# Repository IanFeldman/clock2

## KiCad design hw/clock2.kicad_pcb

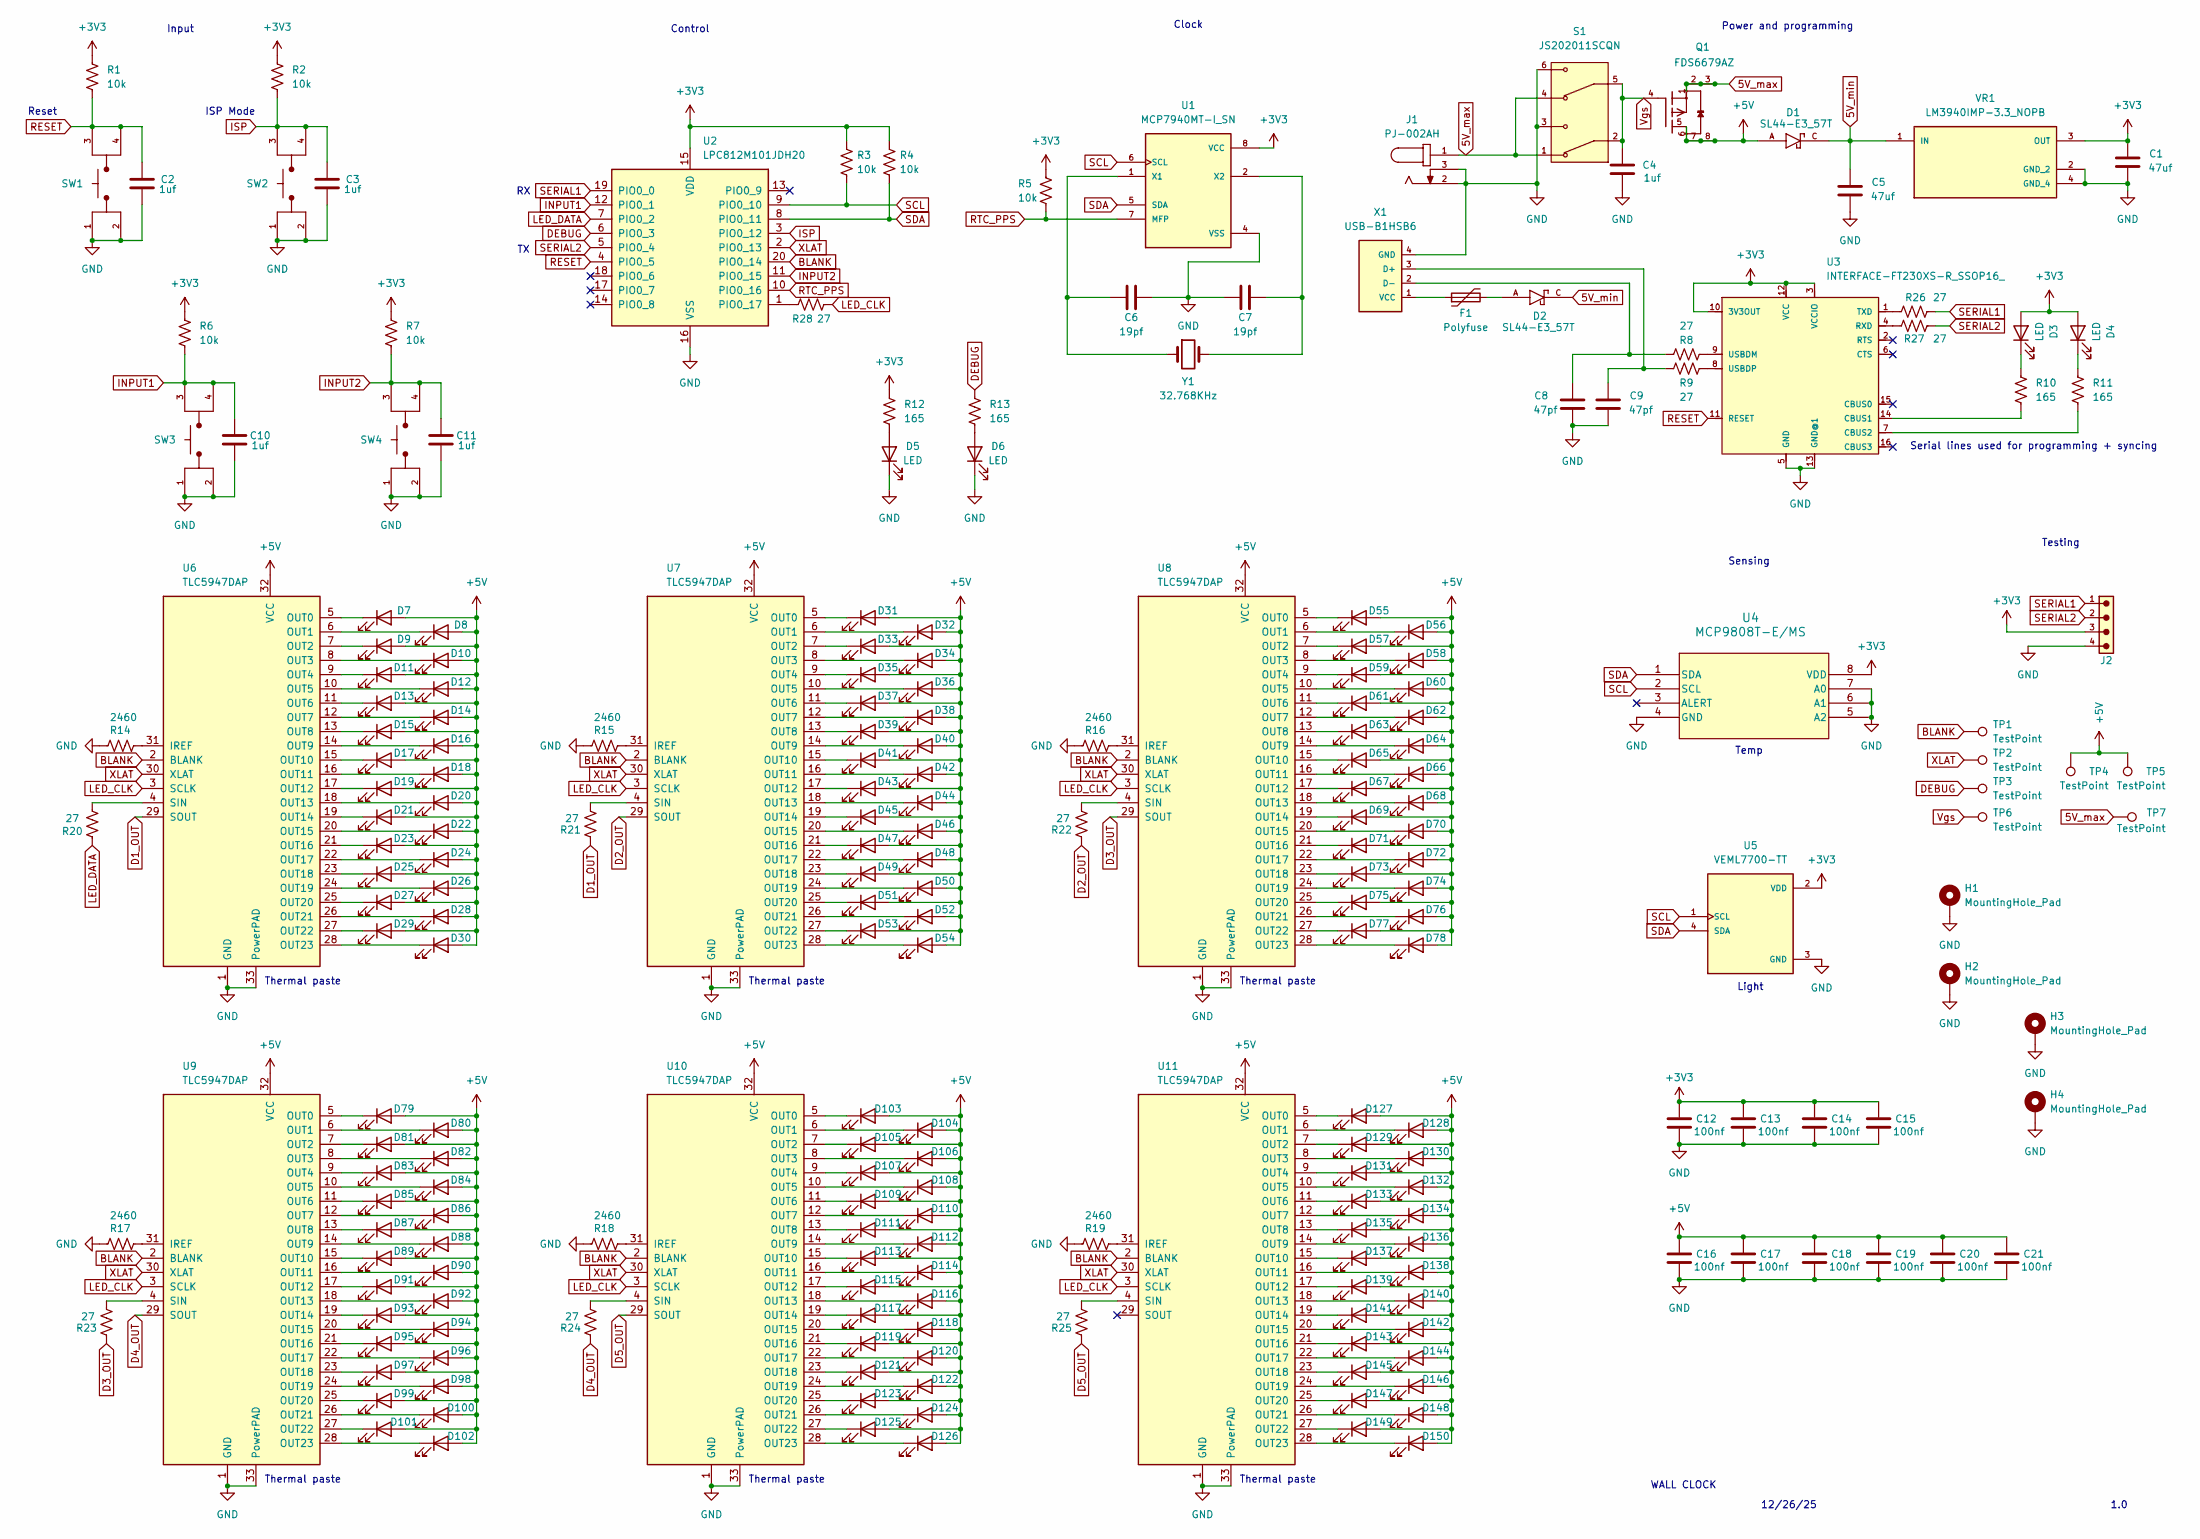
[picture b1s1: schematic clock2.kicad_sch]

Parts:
C1, C5: 47uf; C_0805_2012Metric
C2, C3, C4, C10, C11: 1uf; C_0805_2012Metric
C6, C7: 19pf; C_0805_2012Metric
C8, C9: 47pf; C_0805_2012Metric
C12, C13, C14, C15, C16, C17, C18, C19, C20, C21: 100nf; C_0805_2012Metric
D1, D2: SL44-E3_57T; DIOM7959X262N; DigiKey_Part_Number SL44-E3/57TGICT-ND
D3, D4, D5, D6: LED; LED_0805_2012Metric
D7, D8, D9, D10, D11, D12, D13, D14, D15, D16, D17, D18, D19, D20, D21, D22, D23, D24, D25, D26, D27, D28, D29, D30, D31, D32, D33, D34, D35, D36, D37, D38, D39, D40, D41, D42, D43, D44, D45, D46, D47, D48, D49, D50, D51, D52, D53, D54, D55, D56, D57, D58, D59, D60, D61, D62, D63, D64, D65, D66, D67, D68, D69, D70, D71, D72, D73, D74, D75, D76, D77, D78, D79, D80, D81, D82, D83, D84, D85, D86, D87, D88, D89, D90, D91, D92, D93, D94, D95, D96, D97, D98, D99, D100, D101, D102, D103, D104, D105, D106, D107, D108, D109, D110, D111, D112, D113, D114, D115, D116, D117, D118, D119, D120, D121, D122, D123, D124, D125, D126, D127, D128, D129, D130, D131, D132, D133, D134, D135, D136, D137, D138, D139, D140, D141, D142, D143, D144, D145, D146, D147, D148, D149, D150: LED; LED_1206_3216Metric
F1: Polyfuse; Fuse_1206_3216Metric
H1, H2, H3, H4: MountingHole_Pad; MountingHole_3.2mm_M3_DIN965_Pad
J1: PJ-002AH; CUI_PJ-002AH; DigiKey_Part_Number CP-002AH-ND
J2: 6130XX11121_61300411121; 61300411121
Q1: FDS6679AZ; SOIC127P600X175-8N; DigiKey_Part_Number FDS6679AZCT-ND
R1, R2, R3, R4, R5, R6, R7: 10k; R_0805_2012Metric
R8, R9, R20, R21, R22, R23, R24, R25, R26, R27, R28: 27; R_0805_2012Metric
R10, R11, R12, R13: 165; R_0805_2012Metric
R14, R15, R16, R17, R18, R19: 2460; R_0805_2012Metric
S1: JS202011SCQN; SW_JS202011SCQN; PARTREV 1.01
SW1, SW2, SW3, SW4: TL3305AF260QG; SW_TL3305AF260QG; PARTREV C
TP1, TP2, TP3, TP4, TP5, TP6, TP7: TestPoint; HARWIN_S1751-46R
U1: MCP7940MT-I_SN; SOIC127P600X175-8N
U2: LPC812M101JDH20; TSSOP-20_4.4x6.5mm_P0.65mm
U3: INTERFACE-FT230XS-R_SSOP16_; SSOP16-0.635-5X4MM; MPN FT230XS-R
U4: MCP9808T-E/MS; MCP9808T
U5: VEML7700-TT; XDCR_VEML7700-TT; PARTREV 1.6; DigiKey_Part_Number 751-VEML7700-TTCT-ND
U6, U7, U8, U9, U10, U11: TLC5947DAP; HTSSOP-32-1EP_6.1x11mm_P0.65mm_EP5.2x11mm_Mask4.11x4.36mm_T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
VR1: LM3940IMP-3.3_NOPB; VREG_LM3940IMP-3.3_NOPB; PARTREV G
X1: USB-B1HSB6; OST_USB-B1HSB6; DigiKey_Part_Number ED2983-ND
Y1: 32.768KHz; XTAL_ECS-.327-12.5-34RR-TR

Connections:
5V_max: J1.1, Q1.1, Q1.2, Q1.3, S1.1, S1.4, TP7.1
5V_min: C5.2, D1.C, D2.C, VR1.1 (IN)
+3V3: C1.2, C12.2, C13.2, C14.2, C15.2, D3.2 (A), D4.2 (A), J2.3, R1.2, R2.2, R3.2, R4.2, R5.2, R6.2, R7.2, R12.2, U1.8 (VCC), U2.15 (VDD), U3.3 (VCCIO), U3.10 (3V3OUT), U3.12 (VCC), U4.8 (VDD), U5.2 (VDD), VR1.3 (OUT)
+5V: C16.2, C17.2, C18.2, C19.2, C20.2, C21.2, D1.A, D7.2 (A), D8.2 (A), D9.2 (A), D10.2 (A), D11.2 (A), D12.2 (A), D13.2 (A), D14.2 (A), D15.2 (A), D16.2 (A), D17.2 (A), D18.2 (A), D19.2 (A), D20.2 (A), D21.2 (A), D22.2 (A), D23.2 (A), D24.2 (A), D25.2 (A), D26.2 (A), D27.2 (A), D28.2 (A), D29.2 (A), D30.2 (A), D31.2 (A), D32.2 (A), D33.2 (A), D34.2 (A), D35.2 (A), D36.2 (A), D37.2 (A), D38.2 (A), D39.2 (A), D40.2 (A), D41.2 (A), D42.2 (A), D43.2 (A), D44.2 (A), D45.2 (A), D46.2 (A), D47.2 (A), D48.2 (A), D49.2 (A), D50.2 (A), D51.2 (A), D52.2 (A), D53.2 (A), D54.2 (A), D55.2 (A), D56.2 (A), D57.2 (A), D58.2 (A), D59.2 (A), D60.2 (A), D61.2 (A), D62.2 (A), D63.2 (A), D64.2 (A), D65.2 (A), D66.2 (A), D67.2 (A), D68.2 (A), D69.2 (A), D70.2 (A), D71.2 (A), D72.2 (A), D73.2 (A), D74.2 (A), D75.2 (A), D76.2 (A), D77.2 (A), D78.2 (A), D79.2 (A), D80.2 (A), D81.2 (A), D82.2 (A), D83.2 (A), D84.2 (A), D85.2 (A), D86.2 (A), D87.2 (A), D88.2 (A), D89.2 (A), D90.2 (A), D91.2 (A), D92.2 (A), D93.2 (A), D94.2 (A), D95.2 (A), D96.2 (A), D97.2 (A), D98.2 (A), D99.2 (A), D100.2 (A), D101.2 (A), D102.2 (A), D103.2 (A), D104.2 (A), D105.2 (A), D106.2 (A), D107.2 (A), D108.2 (A), D109.2 (A), D110.2 (A), D111.2 (A), D112.2 (A), D113.2 (A), D114.2 (A), D115.2 (A), D116.2 (A), D117.2 (A), D118.2 (A), D119.2 (A), D120.2 (A), D121.2 (A), D122.2 (A), D123.2 (A), D124.2 (A), D125.2 (A), D126.2 (A), D127.2 (A), D128.2 (A), D129.2 (A), D130.2 (A), D131.2 (A), D132.2 (A), D133.2 (A), D134.2 (A), D135.2 (A), D136.2 (A), D137.2 (A), D138.2 (A), D139.2 (A), D140.2 (A), D141.2 (A), D142.2 (A), D143.2 (A), D144.2 (A), D145.2 (A), D146.2 (A), D147.2 (A), D148.2 (A), D149.2 (A), D150.2 (A), Q1.5, Q1.6, Q1.7, Q1.8, TP4.1, TP5.1, U6.32 (VCC), U7.32 (VCC), U8.32 (VCC), U9.32 (VCC), U10.32 (VCC), U11.32 (VCC)
BLANK: TP1.1, U2.20 (PIO0_14), U6.2 (BLANK), U7.2 (BLANK), U8.2 (BLANK), U9.2 (BLANK), U10.2 (BLANK), U11.2 (BLANK)
D1_OUT: R21.2, U6.29 (SOUT)
D2_OUT: R22.2, U7.29 (SOUT)
D3_OUT: R23.2, U8.29 (SOUT)
D4_OUT: R24.2, U9.29 (SOUT)
D5_OUT: R25.2, U10.29 (SOUT)
DEBUG: R13.2, TP3.1, U2.6 (PIO0_3)
GND: C1.1, C2.2, C3.2, C4.1, C5.1, C6.2, C7.1, C8.1, C9.1, C10.2, C11.2, C12.1, C13.1, C14.1, C15.1, C16.1, C17.1, C18.1, C19.1, C20.1, C21.1, D5.1 (K), D6.1 (K), H1.1, H2.1, H3.1, H4.1, J1.2, J1.3, J2.4, R14.1, R15.1, R16.1, R17.1, R18.1, R19.1, S1.3, S1.6, SW1.1, SW1.2, SW2.1, SW2.2, SW3.1, SW3.2, SW4.1, SW4.2, U1.4 (VSS), U2.16 (VSS), U3.5 (GND), U3.13 (GND@1), U4.4 (GND), U4.5 (A2), U4.6 (A1), U4.7 (A0), U5.3 (GND), U6.1 (GND), U6.33 (PowerPAD), U7.1 (GND), U7.33 (PowerPAD), U8.1 (GND), U8.33 (PowerPAD), U9.1 (GND), U9.33 (PowerPAD), U10.1 (GND), U10.33 (PowerPAD), U11.1 (GND), U11.33 (PowerPAD), VR1.2 (GND_2), VR1.4 (GND_4), X1.4 (GND)
INPUT1: C10.1, R6.1, SW3.3, SW3.4, U2.12 (PIO0_1)
INPUT2: C11.1, R7.1, SW4.3, SW4.4, U2.11 (PIO0_15)
ISP: C3.1, R2.1, SW2.3, SW2.4, U2.3 (PIO0_12)
LED_CLK: R28.2, U6.3 (SCLK), U7.3 (SCLK), U8.3 (SCLK), U9.3 (SCLK), U10.3 (SCLK), U11.3 (SCLK)
LED_DATA: R20.2, U2.7 (PIO0_2)
unnamed: D2.A, F1.2
unnamed: D3.1 (K), R10.2
unnamed: D4.1 (K), R11.2
unnamed: D5.2 (A), R12.1
unnamed: D6.2 (A), R13.1
unnamed: D7.1 (K), U6.5 (OUT0)
unnamed: D8.1 (K), U6.6 (OUT1)
unnamed: D9.1 (K), U6.7 (OUT2)
unnamed: D10.1 (K), U6.8 (OUT3)
unnamed: D11.1 (K), U6.9 (OUT4)
unnamed: D12.1 (K), U6.10 (OUT5)
unnamed: D13.1 (K), U6.11 (OUT6)
unnamed: D14.1 (K), U6.12 (OUT7)
unnamed: D15.1 (K), U6.13 (OUT8)
unnamed: D16.1 (K), U6.14 (OUT9)
unnamed: D17.1 (K), U6.15 (OUT10)
unnamed: D18.1 (K), U6.16 (OUT11)
unnamed: D19.1 (K), U6.17 (OUT12)
unnamed: D20.1 (K), U6.18 (OUT13)
unnamed: D21.1 (K), U6.19 (OUT14)
unnamed: D22.1 (K), U6.20 (OUT15)
unnamed: D23.1 (K), U6.21 (OUT16)
unnamed: D24.1 (K), U6.22 (OUT17)
unnamed: D25.1 (K), U6.23 (OUT18)
unnamed: D26.1 (K), U6.24 (OUT19)
unnamed: D27.1 (K), U6.25 (OUT20)
unnamed: D28.1 (K), U6.26 (OUT21)
unnamed: D29.1 (K), U6.27 (OUT22)
unnamed: D30.1 (K), U6.28 (OUT23)
unnamed: D31.1 (K), U7.5 (OUT0)
unnamed: D32.1 (K), U7.6 (OUT1)
unnamed: D33.1 (K), U7.7 (OUT2)
unnamed: D34.1 (K), U7.8 (OUT3)
unnamed: D35.1 (K), U7.9 (OUT4)
unnamed: D36.1 (K), U7.10 (OUT5)
unnamed: D37.1 (K), U7.11 (OUT6)
unnamed: D38.1 (K), U7.12 (OUT7)
unnamed: D39.1 (K), U7.13 (OUT8)
unnamed: D40.1 (K), U7.14 (OUT9)
unnamed: D41.1 (K), U7.15 (OUT10)
unnamed: D42.1 (K), U7.16 (OUT11)
unnamed: D43.1 (K), U7.17 (OUT12)
unnamed: D44.1 (K), U7.18 (OUT13)
unnamed: D45.1 (K), U7.19 (OUT14)
unnamed: D46.1 (K), U7.20 (OUT15)
unnamed: D47.1 (K), U7.21 (OUT16)
unnamed: D48.1 (K), U7.22 (OUT17)
unnamed: D49.1 (K), U7.23 (OUT18)
unnamed: D50.1 (K), U7.24 (OUT19)
unnamed: D51.1 (K), U7.25 (OUT20)
unnamed: D52.1 (K), U7.26 (OUT21)
unnamed: D53.1 (K), U7.27 (OUT22)
unnamed: D54.1 (K), U7.28 (OUT23)
unnamed: D55.1 (K), U8.5 (OUT0)
unnamed: D56.1 (K), U8.6 (OUT1)
unnamed: D57.1 (K), U8.7 (OUT2)
unnamed: D58.1 (K), U8.8 (OUT3)
unnamed: D59.1 (K), U8.9 (OUT4)
unnamed: D60.1 (K), U8.10 (OUT5)
unnamed: D61.1 (K), U8.11 (OUT6)
unnamed: D62.1 (K), U8.12 (OUT7)
unnamed: D63.1 (K), U8.13 (OUT8)
unnamed: D64.1 (K), U8.14 (OUT9)
unnamed: D65.1 (K), U8.15 (OUT10)
unnamed: D66.1 (K), U8.16 (OUT11)
unnamed: D67.1 (K), U8.17 (OUT12)
unnamed: D68.1 (K), U8.18 (OUT13)
unnamed: D69.1 (K), U8.19 (OUT14)
unnamed: D70.1 (K), U8.20 (OUT15)
unnamed: D71.1 (K), U8.21 (OUT16)
unnamed: D72.1 (K), U8.22 (OUT17)
unnamed: D73.1 (K), U8.23 (OUT18)
unnamed: D74.1 (K), U8.24 (OUT19)
unnamed: D75.1 (K), U8.25 (OUT20)
unnamed: D76.1 (K), U8.26 (OUT21)
unnamed: D77.1 (K), U8.27 (OUT22)
unnamed: D78.1 (K), U8.28 (OUT23)
unnamed: D79.1 (K), U9.5 (OUT0)
unnamed: D80.1 (K), U9.6 (OUT1)
unnamed: D81.1 (K), U9.7 (OUT2)
unnamed: D82.1 (K), U9.8 (OUT3)
unnamed: D83.1 (K), U9.9 (OUT4)
unnamed: D84.1 (K), U9.10 (OUT5)
unnamed: D85.1 (K), U9.11 (OUT6)
unnamed: D86.1 (K), U9.12 (OUT7)
unnamed: D87.1 (K), U9.13 (OUT8)
unnamed: D88.1 (K), U9.14 (OUT9)
unnamed: D89.1 (K), U9.15 (OUT10)
unnamed: D90.1 (K), U9.16 (OUT11)
unnamed: D91.1 (K), U9.17 (OUT12)
unnamed: D92.1 (K), U9.18 (OUT13)
unnamed: D93.1 (K), U9.19 (OUT14)
unnamed: D94.1 (K), U9.20 (OUT15)
unnamed: D95.1 (K), U9.21 (OUT16)
unnamed: D96.1 (K), U9.22 (OUT17)
unnamed: D97.1 (K), U9.23 (OUT18)
unnamed: D98.1 (K), U9.24 (OUT19)
unnamed: D99.1 (K), U9.25 (OUT20)
unnamed: D100.1 (K), U9.26 (OUT21)
unnamed: D101.1 (K), U9.27 (OUT22)
unnamed: D102.1 (K), U9.28 (OUT23)
unnamed: D103.1 (K), U10.5 (OUT0)
unnamed: D104.1 (K), U10.6 (OUT1)
unnamed: D105.1 (K), U10.7 (OUT2)
unnamed: D106.1 (K), U10.8 (OUT3)
unnamed: D107.1 (K), U10.9 (OUT4)
unnamed: D108.1 (K), U10.10 (OUT5)
unnamed: D109.1 (K), U10.11 (OUT6)
unnamed: D110.1 (K), U10.12 (OUT7)
unnamed: D111.1 (K), U10.13 (OUT8)
unnamed: D112.1 (K), U10.14 (OUT9)
unnamed: D113.1 (K), U10.15 (OUT10)
unnamed: D114.1 (K), U10.16 (OUT11)
unnamed: D115.1 (K), U10.17 (OUT12)
unnamed: D116.1 (K), U10.18 (OUT13)
unnamed: D117.1 (K), U10.19 (OUT14)
unnamed: D118.1 (K), U10.20 (OUT15)
unnamed: D119.1 (K), U10.21 (OUT16)
unnamed: D120.1 (K), U10.22 (OUT17)
unnamed: D121.1 (K), U10.23 (OUT18)
unnamed: D122.1 (K), U10.24 (OUT19)
unnamed: D123.1 (K), U10.25 (OUT20)
unnamed: D124.1 (K), U10.26 (OUT21)
unnamed: D125.1 (K), U10.27 (OUT22)
unnamed: D126.1 (K), U10.28 (OUT23)
unnamed: D127.1 (K), U11.5 (OUT0)
unnamed: D128.1 (K), U11.6 (OUT1)
unnamed: D129.1 (K), U11.7 (OUT2)
unnamed: D130.1 (K), U11.8 (OUT3)
unnamed: D131.1 (K), U11.9 (OUT4)
unnamed: D132.1 (K), U11.10 (OUT5)
unnamed: D133.1 (K), U11.11 (OUT6)
unnamed: D134.1 (K), U11.12 (OUT7)
unnamed: D135.1 (K), U11.13 (OUT8)
unnamed: D136.1 (K), U11.14 (OUT9)
unnamed: D137.1 (K), U11.15 (OUT10)
unnamed: D138.1 (K), U11.16 (OUT11)
unnamed: D139.1 (K), U11.17 (OUT12)
unnamed: D140.1 (K), U11.18 (OUT13)
unnamed: D141.1 (K), U11.19 (OUT14)
unnamed: D142.1 (K), U11.20 (OUT15)
unnamed: D143.1 (K), U11.21 (OUT16)
unnamed: D144.1 (K), U11.22 (OUT17)
unnamed: D145.1 (K), U11.23 (OUT18)
unnamed: D146.1 (K), U11.24 (OUT19)
unnamed: D147.1 (K), U11.25 (OUT20)
unnamed: D148.1 (K), U11.26 (OUT21)
unnamed: D149.1 (K), U11.27 (OUT22)
unnamed: D150.1 (K), U11.28 (OUT23)
unnamed: C6.1, U1.1 (X1), Y1.1
unnamed: C7.2, U1.2 (X2), Y1.2
unnamed: R28.1, U2.1 (PIO0_17)
unnamed: R10.1, U3.14 (CBUS1)
unnamed: R11.1, U3.7 (CBUS2)
unnamed: R27.2, U3.4 (RXD)
unnamed: R26.2, U3.1 (TXD)
unnamed: R8.1, U3.9 (USBDM)
unnamed: R9.2, U3.8 (USBDP)
unnamed: R14.2, U6.31 (IREF)
unnamed: R20.1, U6.4 (SIN)
unnamed: R15.2, U7.31 (IREF)
unnamed: R21.1, U7.4 (SIN)
unnamed: R16.2, U8.31 (IREF)
unnamed: R22.1, U8.4 (SIN)
unnamed: R17.2, U9.31 (IREF)
unnamed: R23.1, U9.4 (SIN)
unnamed: R18.2, U10.31 (IREF)
unnamed: R24.1, U10.4 (SIN)
unnamed: R19.2, U11.31 (IREF)
unnamed: R25.1, U11.4 (SIN)
unnamed: C9.2, R9.1, X1.3 (D+)
unnamed: C8.2, R8.2, X1.2 (D-)
unnamed: F1.1, X1.1 (VCC)
RESET: C2.1, R1.1, SW1.3, SW1.4, U2.4 (PIO0_5), U3.11 (RESET)
RTC_PPS: R5.1, U1.7 (MFP), U2.10 (PIO0_16)
SCL: R3.1, U1.6 (SCL), U2.9 (PIO0_10), U4.2 (SCL), U5.1 (SCL)
SDA: R4.1, U1.5 (SDA), U2.8 (PIO0_11), U4.1 (SDA), U5.4 (SDA)
SERIAL1: J2.1, R26.1, U2.19 (PIO0_0)
SERIAL2: J2.2, R27.1, U2.5 (PIO0_4)
Vgs: C4.2, Q1.4, S1.2, S1.5, TP6.1
XLAT: TP2.1, U2.2 (PIO0_13), U6.30 (XLAT), U7.30 (XLAT), U8.30 (XLAT), U9.30 (XLAT), U10.30 (XLAT), U11.30 (XLAT)

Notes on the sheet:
Thermal paste
Clock
Light
12/26/25
ISP Mode
Testing
Input
Power and programming
WALL CLOCK
Reset
Serial lines used for programming + syncing
Sensing
Temp
1.0
Control

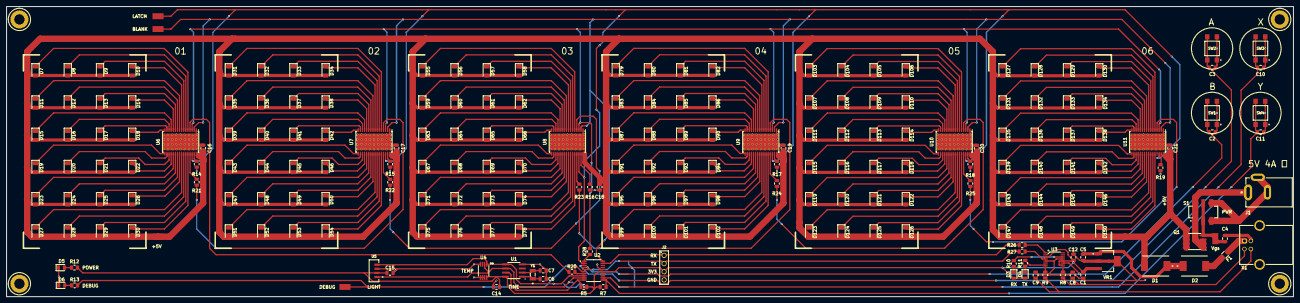
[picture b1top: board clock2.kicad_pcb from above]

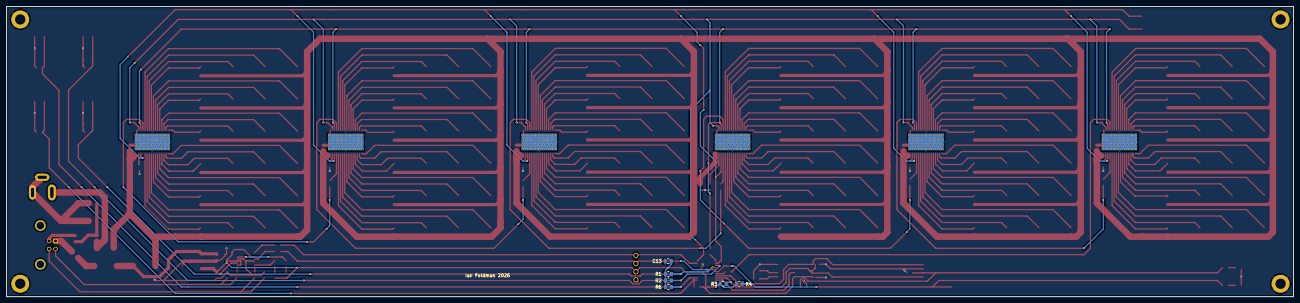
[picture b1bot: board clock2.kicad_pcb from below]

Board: 2 copper layers, 399.2 x 90.0 mm, 233 parts (6 on the bottom side), 198 nets.

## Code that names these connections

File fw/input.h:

#ifndef INPUT_H
#define INPUT_H

#define GPIO_CLK_EN 6

/* Debug output */
#define DEBUG_PIN 3

/* Pulse per second */
#define PPS_PIN 16
#define PPS_IRQ 0    /* PININT0_IRQ */

/* X */
#define INPUT1_PIN 1
#define INPUT1_IRQ 1 /* PININT1_IRQ */

/* Y */
#define INPUT2_PIN 15
#define INPUT2_IRQ 2 /* PININT2_IRQ */

/* A + ISP */
#define INPUT3_PIN 12
#define INPUT3_IRQ 3 /* PININT3_IRQ */

/* B + RESET */
#define INPUT4_PIN 5
#define INPUT4_IRQ 4 /* PININT4_IRQ */

#define DEBOUNCE_COUNT 1000

extern volatile int pps_flag;
extern volatile int input1_flag;
extern volatile int input2_flag;
extern volatile int input3_flag;
extern volatile int input4_flag;

void input_initialize(void);
int input_debounce(int input_pin, int *flag);
void input_toggle_debug(void);
void PININT0_IRQHandler(void);
void PININT1_IRQHandler(void);
void PININT2_IRQHandler(void);
void PININT3_IRQHandler(void);
void PININT4_IRQHandler(void);

#endif /* INPUT_H */

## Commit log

2026-01-30 Add hardware
2026-02-02 Import clock1 fw
2026-02-05 Enable debug pin
2026-02-06 Refactor input handling
2026-02-06 Debug square pps
2026-02-08 Display initialize
2026-02-08 Segment output
2026-02-08 Successful segment update
2026-02-11 Rework display write
2026-02-18 Letters
2026-02-18 Numbers
2026-02-18 Telling time
2026-02-18 Telling temp
2026-02-18 Rename time and temp structs
2026-02-18 Change display write to use uint8
2026-02-22 Support light sense
2026-02-27 Support modes and time setting over uart
2026-02-28 Wave animation
2026-04-11 Set time with buttons
